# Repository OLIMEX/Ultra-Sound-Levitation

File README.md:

# Ultra-Sound-Levitation
Ultra Sound Levitation board with two speakers and potentiometer

Product page: https://www.olimex.com/Products/Soldering-Kits/Ultra-Sound-Levitation/open-source-hardware

## License
* Hardware is released under CERN Open Hardware Licence Version 2 - Strongly Reciprocal https://spdx.org/licenses/CERN-OHL-S-2.0.html
* Software is released under GPL3 License
* Documentation is released under CC BY-SA 4.0 https://creativecommons.org/licenses/by-sa/4.0/

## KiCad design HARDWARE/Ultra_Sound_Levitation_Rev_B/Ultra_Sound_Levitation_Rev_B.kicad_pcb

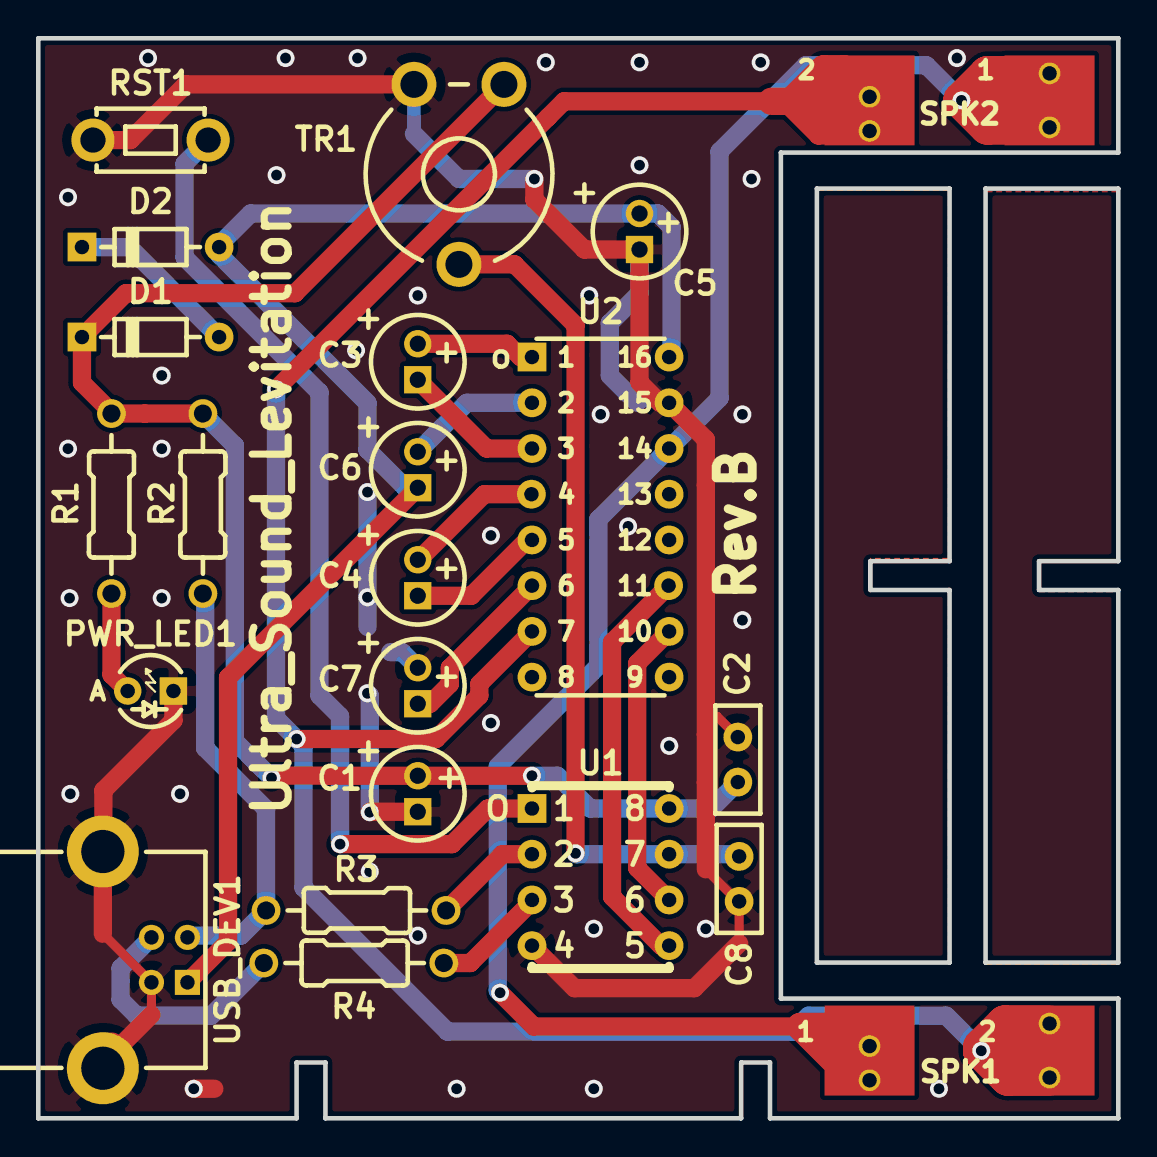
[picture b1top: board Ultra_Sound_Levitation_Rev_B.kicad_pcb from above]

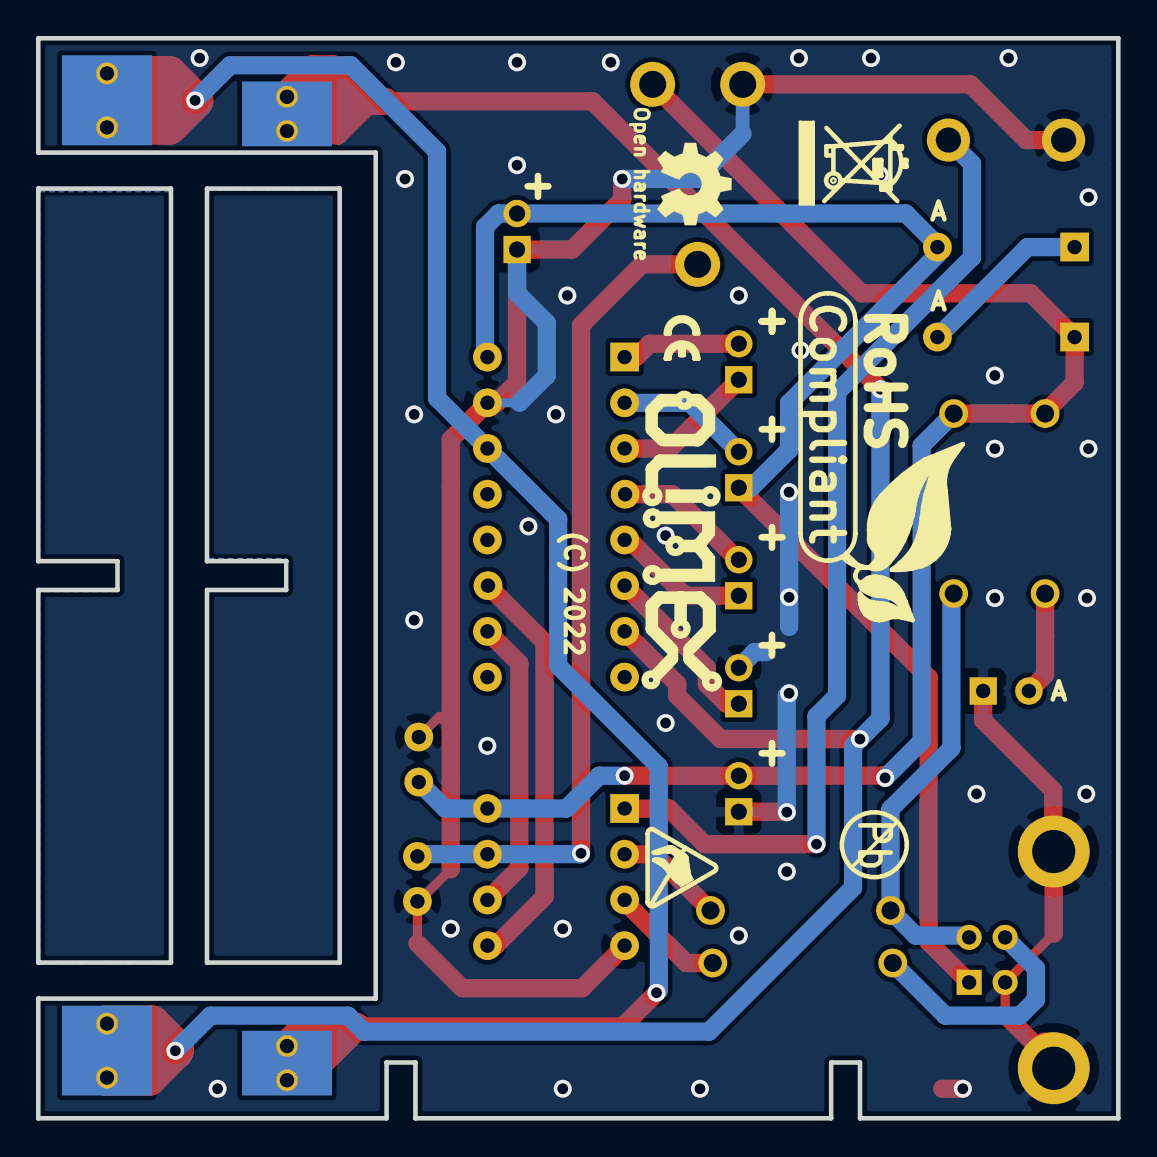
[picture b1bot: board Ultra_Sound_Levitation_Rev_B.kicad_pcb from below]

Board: 2 copper layers, 60.0 x 60.0 mm, 29 parts (7 on the bottom side), 21 nets.

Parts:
C1, C3, C4, C5, C6, C7: 4.7uF/50V; CPOL-RM2mm_5x11mm_PTH
C2, C8: 100nF/25V/2010; C2010
D1, D2: 1N4148/DO35; DO35_1K_2A
Logo_OLIMEX_TB: Logo_OLIMEX_TB
PWR_LED1: LED/3mm/Green; LED-3mm-PTH-KA
R1, R2: 1.5k/0.25W; R_0.25W_PTH
R3, R4: 22R/0.25W; R_0.25W_PTH
RST1: T1101GP(6x3x4.3mm); T1101_GP-6x3x4.3
SPK1, SPK2: ULTRASONIC?; SPEAKER_ULTRASONIC
Sign_Antistatic_Small: Sign_Antistatic; Sign_Antistatic_4.5mmX2.8mm
Sign_CE_Small: CE_Sign_Small
Sign_OSHW_7.3x6.0mm: Sign_OSHW_7.3x6.0mm; Sign_OSHW_7.3x6.0mmn
Sign_PB-Free: Sign_PB-Free
Sign_RecycleBin_1: Sign_RecycleBin_1
Sign_RoHS_1: Sign_RoHS_1
TR1: TRIM PIHER PT10LV 10K+KNOB; TRIM_PIHER_PT10LV
U1: ATtiny85-20PU+(DIL-8); PDIP-8
U2: MAX232EN+(DIL-16); PDIP-16
USB_DEV1: USB-B(USB-SRWH-4B-LF)

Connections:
+5V: C5.1, C6.2, D2.2, U2.16, USB_DEV1.1
GND: C1.2, C2.2, C5.2, C7.1, C8.2, PWR_LED1.1, RST1.1, TR1.3, U1.4, U2.15, USB_DEV1.0, USB_DEV1.4
unnamed: C1.1, C2.1, D1.1, R1.1, R2.1, TR1.1, U1.8
unnamed: C3.1, U2.1
unnamed: C3.2, U2.3
unnamed: C4.1, U2.4
unnamed: C4.2, U2.5
unnamed: C6.1, U2.2
unnamed: C7.2, U2.6
unnamed: C8.1, TR1.2, U1.7
unnamed: D1.2, D2.1
unnamed: PWR_LED1.2, R1.2
unnamed: R2.2, R3.1, USB_DEV1.2
unnamed: R3.2, U1.2
unnamed: R4.1, USB_DEV1.3
unnamed: R4.2, U1.3
unnamed: RST1.2, U1.1
PB0_OC0A: U1.5, U2.11
PB1_OCOB: U1.6, U2.10
spout1: SPK1.1, SPK2.1, U2.14
spout2: SPK1.2, SPK2.2, U2.7

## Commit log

2022-10-12 initial upload

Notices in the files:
HARDWARE/Ultra_Sound_Levitation_Rev_B/Ultra_Sound_Levitation_Rev_B.kicad_pcb:
(C) 2022
